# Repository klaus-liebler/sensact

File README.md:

# sensact
Smarthome system - hardware, firmware, visualization

## Architektur
* Verteiltes System. Modellbasierte Codeerzeugung.
* Grundlage ist `firmware/sensact_firmware/builder/Models/` (Phase `GenerateModelFiles`).
  Hier ein Projekt analog Beispielprojekt "Sattlerstrasse16" anlegen (s.
  `firmware/sensact_firmware/docs/build-process.md`).
* Kleinste Einheit ist eine "Application", die eine eindeutige ID besitzt. Beispiele für Applications sind "Taster", "Drehencoder", "Jalousie" oder "PWM-Licht"

## Hardware
1. SensactHS: Hutschienenmontage
1. SensactUP: Unterputzmontage

## Kommunikation zwischen den Knoten
Die Knoten sind über einen gemeinsamen CAN-Bus verbunden.

### Altes Nachrichtenformat ()
TBD

### Neues Nachrichtenformat

Es gibt vier Namespaces für Nachrichten "REQUEST" und "RESPONSE", "EVENT" und "ACKNOWLEDGE". Dies wird mit den beiden LSB des Versions-Namespace-Bytes erklärt (Somit bleiben 64 Versionierungsmöglichkeiten)
Alle vier Namespaces haben ihren eigenen counter. Dieser beginnt bei 0x0 mit der ersten versendeten Nachricht und läuft nach 255 (0xFF) wieder auf 0. Die Ready-Nachricht wird immer mit counter=0x0 übertragen. Sie darf verwendet werden, um die Kommunikations-Session abzubrechen und die counter neu zu starten. Die counter representieren gemeinsames Wissen von Master und Slave  
REQEST (0b00): Vom Master zum Slave.
RESPONSE (0b01): Antwort auf REQUEST
EVENT (0b10): Vom Slave zum Master
ACKNOWLEDGE (0b11): Antwort des Masters auf ein Event

REQUEST
0x00: "HEARTBEAT": Board gibt Heartbeat zurück
0x01: "IDENTIFY: 
0x02: "SEND_CAN":

RESPONSE
In der Response wird einfach die ID des Requests übernommen. Häufig wird dann ein REQUEST-spezifischer Fehlercode als uint32-t zurück geliefert. Eine 0x0 steht dann per Konvention für eine fehlerfreie Verarbeitung. Ggf. werden in Zukunft WELL_KNOWN_ERROR_CODES definiert.
0x01: UNEXPECTED_COUNTER
0x02: CRC_ERROR

Alle Responses, die nicht nur einen reinen Error-Code, sondern spezifischere Daten zurück liefern, werden im folgenden beschrieben  
0x01: "IDENTIFY": Board gibt Board-Typ u16. NodeID u16 und ID des Chips u96 (?) zurück.

EVENTS
00 "READY" Slave meldet sich nach dem Booten und gibt an, dass er jetzt für Befehle aller Art bereit steht. Beginn einer Session. Alle counter werden auf 0 gesetzt, außer der EVENT_COUNTER - der muss nun auf 1 stehen
02 "CAN_RECEIVED": Slave zeigt an, dass er eine CAN-Nachricht empfangen (besser: auf dem Bus mitgelesen) hat

ACKNOWLEDGES:
Der Slave kann bei ausbleibendem Acknowledge die Nachricht nochmals versenden

## WebUI

### Konzept

Auf einer Website sollen alle Apps einer Node mit commands versehen werden können
Jeder Host hat eine Bedienoberfläche
Problem: Wird die Bedienoberfläche zur Laufzeit von den Hosts und ihren Unterobjekten generiert (a) HTML oder b)JSON) oder kennt die WebUI bereits alle Objekte
Kennt die WebUI die Objekte auch semantisch oder kann Sie nur eine HTML-GUI aufbauen zur Erzeugung von CAN-Bus-Nachrichten 
Denkweise: Die WebUI kann CAN-Nachrichten erzeugen und so an die Node senden, wie sie auch über den CAN-Bus an der Node ankommen würden. Es muss ein JSON generiert werden, das zur Erzeugung einer HTML-UI verwendet werden kann, die dann eben genau diese Nachrichten sendet
Die WebUI kennt bereits alle Applications, die in der Node vorhanden sind. Dazu wird neben der C++-Instanzierung auch TypeScript-Code aufgebaut, der die entsprechenden Objekte aufbaut
Für Buttons und RotEnc gibt es die Möglichkeit, die Beträtigung zu simulieren. Dazu wird dann einfach jene Nachricht auf den MessageBus gelegt, die auch in Wirklichkeit vrsendet wird
An Aktoren können jene Commands versendet werden mitsamt notwendiger Parameter
Für die Erstellung eines Command

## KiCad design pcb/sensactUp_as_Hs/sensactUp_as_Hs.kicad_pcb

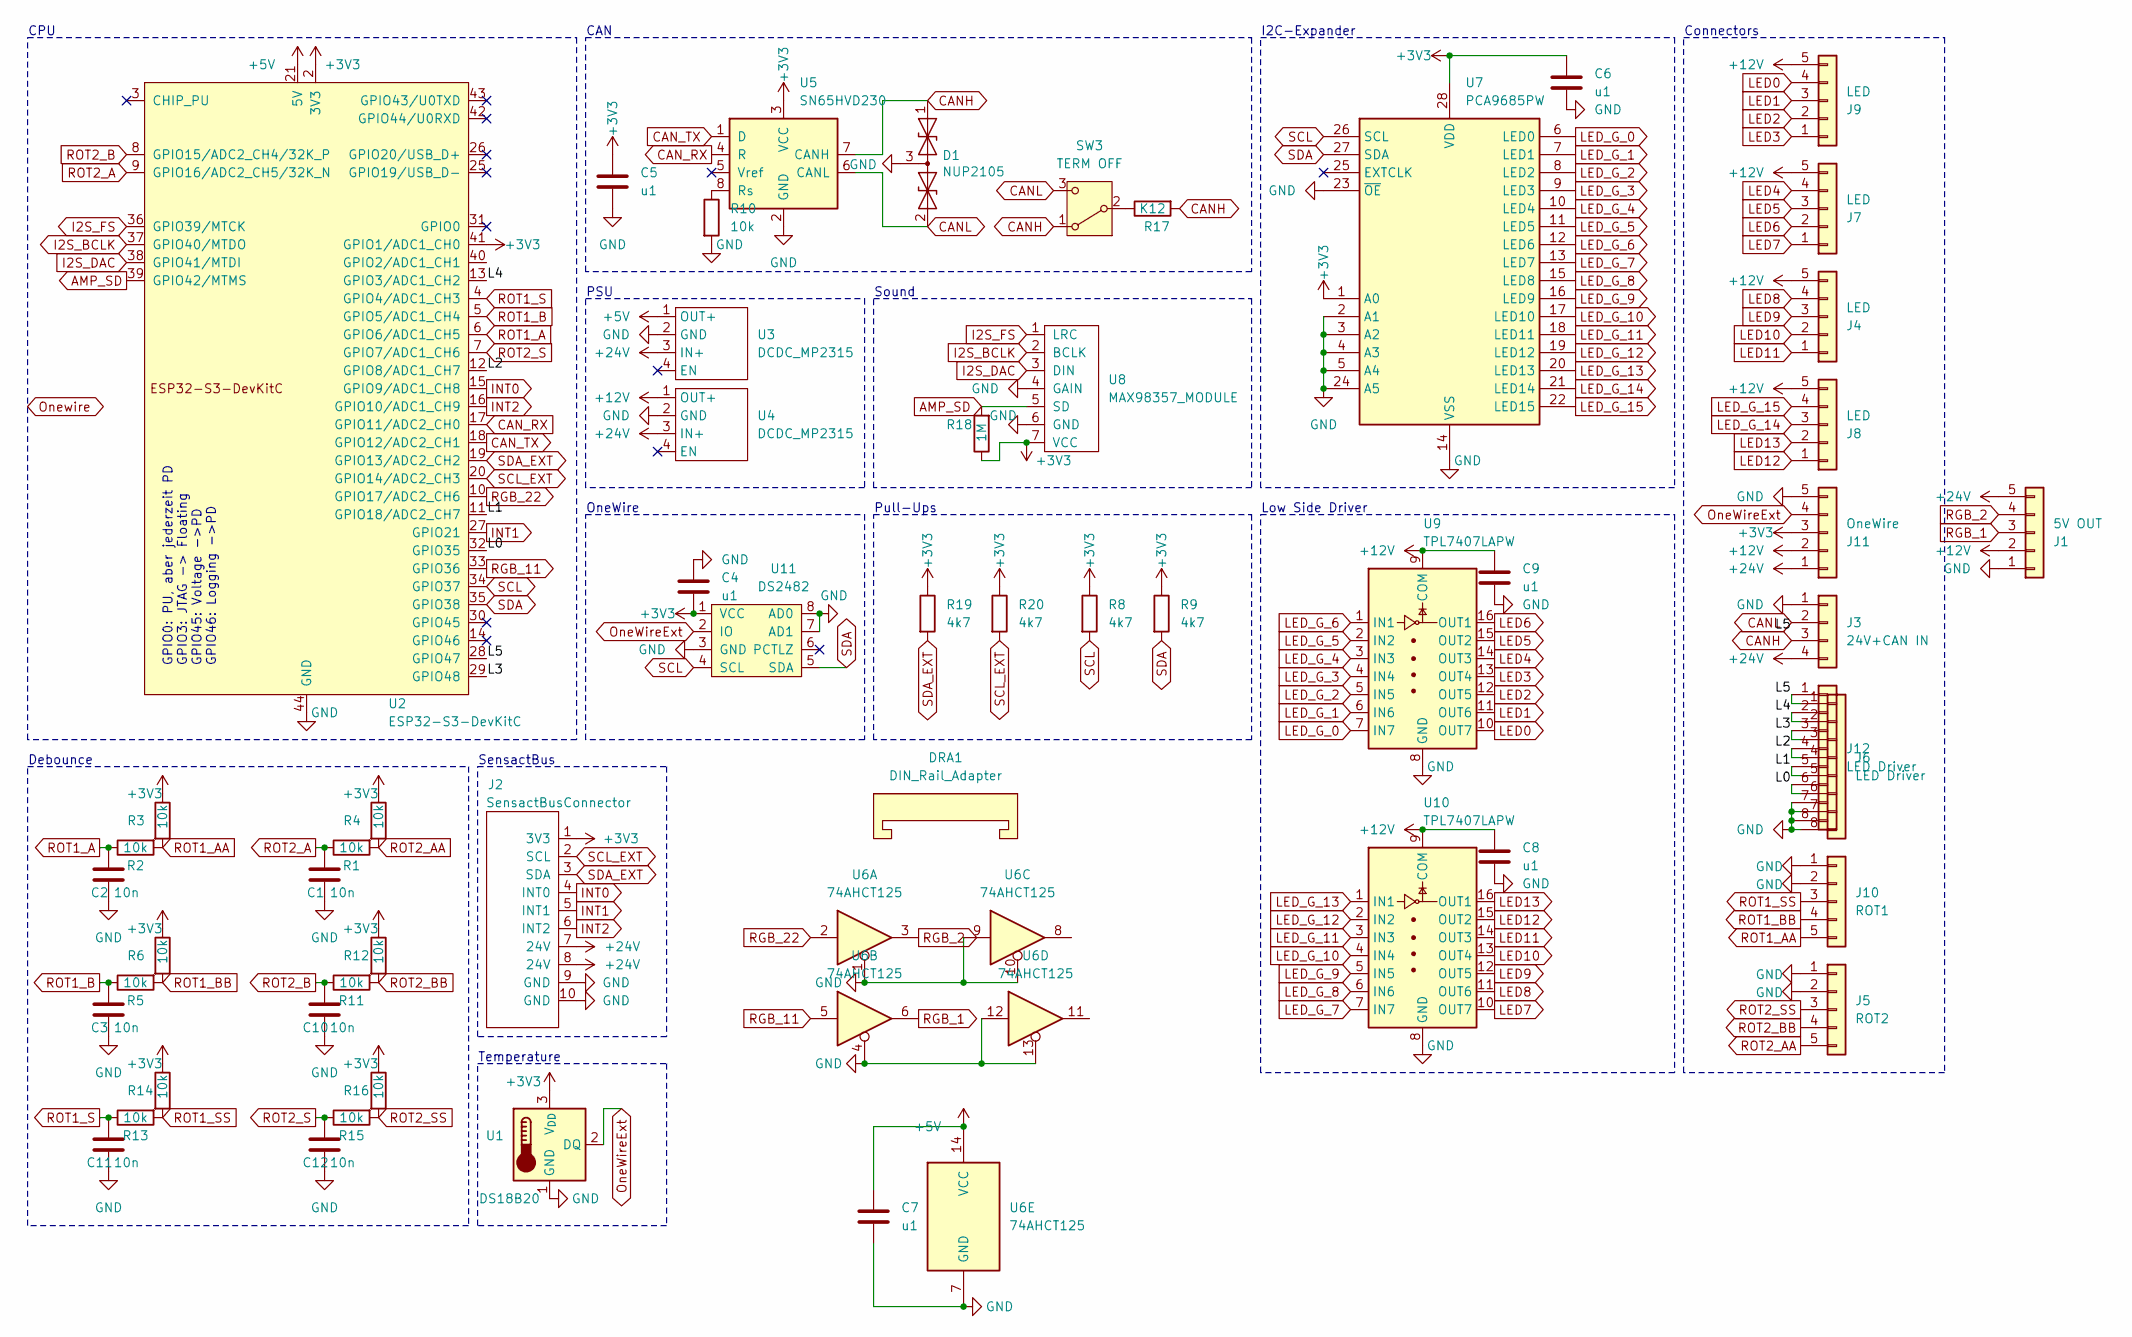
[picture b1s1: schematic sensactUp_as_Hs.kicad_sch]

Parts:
C1, C2, C3, C10, C11, C12: 10n; C_0805_2012Metric_Pad1.18x1.45mm_HandSolder
C4, C5, C6, C7, C8, C9: u1; C_0805_2012Metric_Pad1.18x1.45mm_HandSolder
D1: NUP2105; SOT-23_Handsoldering; MPN NUP2105L
DRA1: DIN_Rail_Adapter; Camdenboss CNMB-6
J1: 5V OUT; PhoenixContact_MCV_1,5_5-G-3.81_1x05_P3.81mm_Vertical_small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
J2: SensactBusConnector; IDC-Header_2x05_P2.54mm_Horizontal
J3: 24V+CAN IN; PhoenixContact_MCV_1,5_4-G-3.5_1x04_P3.50mm_Vertical_smalle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
J4, J7, J8, J9: LED; PhoenixContact_MCV_1,5_5-G-3.81_1x05_P3.81mm_Vertical_small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
J5: ROT2; PhoenixContact_MCV_1,5_5-G-3.81_1x05_P3.81mm_Vertical_small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
J6: LED Driver; PhoenixContact_MC_0,5_8-G-2.5_1x08_P2.50mm_Horizontal
J10: ROT1; PhoenixContact_MCV_1,5_5-G-3.81_1x05_P3.81mm_Vertical_small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
J11: OneWire; PhoenixContact_MCV_1,5_5-G-3.81_1x05_P3.81mm_Vertical_small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
J12: LED Driver; PinHeader_1x08_P2.54mm_Vertical
R1, R2, R3, R4, R5, R6, R10, R11, R12, R13, R14, R15, R16: 10k; R_0805_2012Metric_Pad1.20x1.40mm_HandSolder
R8, R9, R19, R20: 4k7; R_0805_2012Metric_Pad1.20x1.40mm_HandSolder
R17: K12; R_1206_3216Metric_Pad1.30x1.75mm_HandSolder; MPN 1206W4F1200T5E
R18: 1M; R_0805_2012Metric_Pad1.20x1.40mm_HandSolder
SW3: TERM OFF; Switch_SS12D00
U1: DS18B20; TO-92L_HandSolder
U2: ESP32-S3-DevKitC; ESP32-S3 chinese dev board
U3, U4: DCDC_MP2315; DCDC_MP2315_horizontal
U5: SN65HVD230; SOIC-8_3.9x4.9mm_P1.27mm
U6: 74AHCT125; SOIC-14_3.9x8.7mm_P1.27mm_handsolder
U7: PCA9685PW; TSSOP-28_4.4x9.7mm_Pitch0.65mm_handsolder
U8: MAX98357_MODULE; PinHeader_1x07_P2.54mm_Vertical
U9, U10: TPL7407LAPW; TSSOP-16_4.4x5mm_P0.65mm
U11: DS2482; SOIC-8_3.9x4.9mm_P1.27mm_handsolder

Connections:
+3V3: C4.1, C5.1, C6.1, J2.1 (3V3), J11.3, R3.1, R4.1, R6.1, R8.1, R9.1, R12.1, R14.1, R16.1, R18.1, R19.1, R20.1, U1.3 (V_{DD}), U2.1 (3V3), U2.2 (3V3), U2.41 (GPIO1/ADC1_CH0), U5.3 (VCC), U7.1 (A0), U7.28 (VDD), U8.7 (VCC), U11.1 (VCC)
+5V: C7.2, U2.21 (5V), U3.1 (OUT+), U6.14 (VCC)
+12V: C8.1, C9.1, J1.2, J4.5, J7.5, J8.5, J9.5, J11.2, U4.1 (OUT+), U9.9 (COM), U10.9 (COM)
+24V: J1.5, J2.7 (24V), J2.8 (24V), J3.4, J11.1, U3.3 (IN+), U4.3 (IN+)
/L0: J6.6, J12.6, U2.32 (GPIO35)
/L1: J6.5, J12.5, U2.11 (GPIO18/ADC2_CH7)
/L2: J6.4, J12.4, U2.12 (GPIO8/ADC1_CH7)
/L3: J6.3, J12.3, U2.29 (GPIO48)
/L4: J6.2, J12.2, U2.13 (GPIO3/ADC1_CH2)
/L5: J6.1, J12.1, U2.28 (GPIO47)
AMP_SD: R18.2, U2.39 (GPIO42/MTMS), U8.5 (SD)
CANH: D1.1 (A1), J3.3, R17.2, SW3.1 (A), U5.7 (CANH)
CANL: D1.2 (A2), J3.2, SW3.3 (C), U5.6 (CANL)
CAN_RX: U2.17 (GPIO11/ADC2_CH0), U5.4 (R)
CAN_TX: U2.18 (GPIO12/ADC2_CH1), U5.1 (D)
GND: C1.1, C2.1, C3.1, C4.2, C5.2, C6.2, C7.1, C8.2, C9.2, C10.1, C11.1, C12.1, D1.3 (common), J1.1, J2.9 (GND), J2.10 (GND), J3.1, J5.1, J5.2, J6.7, J6.8, J10.1, J10.2, J11.5, J12.7, J12.8, R10.2, U1.1 (GND), U2.22 (GND), U2.23 (GND), U2.24 (GND), U2.44 (GND), U3.2 (GND), U4.2 (GND), U5.2 (GND), U6.1, U6.4, U6.7 (GND), U6.9, U6.10, U6.12, U6.13, U7.2 (A1), U7.3 (A2), U7.4 (A3), U7.5 (A4), U7.14 (VSS), U7.23 (~OE), U7.24 (A5), U8.4 (GAIN), U8.6 (GND), U9.8 (GND), U10.8 (GND), U11.3 (GND), U11.7 (AD1), U11.8 (AD0)
I2S_BCLK: U2.37 (GPIO40/MTDO), U8.2 (BCLK)
I2S_DAC: U2.38 (GPIO41/MTDI), U8.3 (DIN)
I2S_FS: U2.36 (GPIO39/MTCK), U8.1 (LRC)
INT0: J2.4 (INT0), U2.15 (GPIO9/ADC1_CH8)
INT1: J2.5 (INT1), U2.27 (GPIO21)
INT2: J2.6 (INT2), U2.16 (GPIO10/ADC1_CH9)
LED0: J9.4, U9.10 (OUT7)
LED1: J9.3, U9.11 (OUT6)
LED2: J9.2, U9.12 (OUT5)
LED3: J9.1, U9.13 (OUT4)
LED4: J7.4, U9.14 (OUT3)
LED5: J7.3, U9.15 (OUT2)
LED6: J7.2, U9.16 (OUT1)
LED7: J7.1, U10.10 (OUT7)
LED8: J4.4, U10.11 (OUT6)
LED9: J4.3, U10.12 (OUT5)
LED10: J4.2, U10.13 (OUT4)
LED11: J4.1, U10.14 (OUT3)
LED12: J8.1, U10.15 (OUT2)
LED13: J8.2, U10.16 (OUT1)
LED_G_0: U7.6 (LED0), U9.7 (IN7)
LED_G_1: U7.7 (LED1), U9.6 (IN6)
LED_G_2: U7.8 (LED2), U9.5 (IN5)
LED_G_3: U7.9 (LED3), U9.4 (IN4)
LED_G_4: U7.10 (LED4), U9.3 (IN3)
LED_G_5: U7.11 (LED5), U9.2 (IN2)
LED_G_6: U7.12 (LED6), U9.1 (IN1)
LED_G_7: U7.13 (LED7), U10.7 (IN7)
LED_G_8: U7.15 (LED8), U10.6 (IN6)
LED_G_9: U7.16 (LED9), U10.5 (IN5)
LED_G_10: U7.17 (LED10), U10.4 (IN4)
LED_G_11: U7.18 (LED11), U10.3 (IN3)
LED_G_12: U7.19 (LED12), U10.2 (IN2)
LED_G_13: U7.20 (LED13), U10.1 (IN1)
LED_G_14: J8.3, U7.21 (LED14)
LED_G_15: J8.4, U7.22 (LED15)
unnamed: R17.1, SW3.2 (B)
unnamed: R10.1, U5.8 (Rs)
OneWireExt: J11.4, U1.2 (DQ), U11.2 (IO)
RGB_1: J1.3, U6.6
RGB_2: J1.4, U6.3
RGB_11: U2.33 (GPIO36), U6.5
RGB_22: U2.10 (GPIO17/ADC2_CH6), U6.2
ROT1_A: C2.2, R2.1, U2.6 (GPIO6/ADC1_CH5)
ROT1_AA: J10.5, R2.2, R3.2
ROT1_B: C3.2, R5.1, U2.5 (GPIO5/ADC1_CH4)
ROT1_BB: J10.4, R5.2, R6.2
ROT1_S: C11.2, R13.1, U2.4 (GPIO4/ADC1_CH3)
ROT1_SS: J10.3, R13.2, R14.2
ROT2_A: C1.2, R1.1, U2.9 (GPIO16/ADC2_CH5/32K_N)
ROT2_AA: J5.5, R1.2, R4.2
ROT2_B: C10.2, R11.1, U2.8 (GPIO15/ADC2_CH4/32K_P)
ROT2_BB: J5.4, R11.2, R12.2
ROT2_S: C12.2, R15.1, U2.7 (GPIO7/ADC1_CH6)
ROT2_SS: J5.3, R15.2, R16.2
SCL: R8.2, U2.34 (GPIO37), U7.26 (SCL), U11.4 (SCL)
SCL_EXT: J2.2 (SCL), R20.2, U2.20 (GPIO14/ADC2_CH3)
SDA: R9.2, U2.35 (GPIO38), U7.27 (SDA), U11.5 (SDA)
SDA_EXT: J2.3 (SDA), R19.2, U2.19 (GPIO13/ADC2_CH2)

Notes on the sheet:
GPIO0: PU, aber jederzeit PD GPIO3: JTAG -> Floating GPIO45: Voltage ->PD GPIO46: Logging ->PD
Low Side Driver
OneWire
Sound
CAN
Pull-Ups
I2C-Expander
Debounce
SensactBus
CPU
PSU
Connectors
Temperature

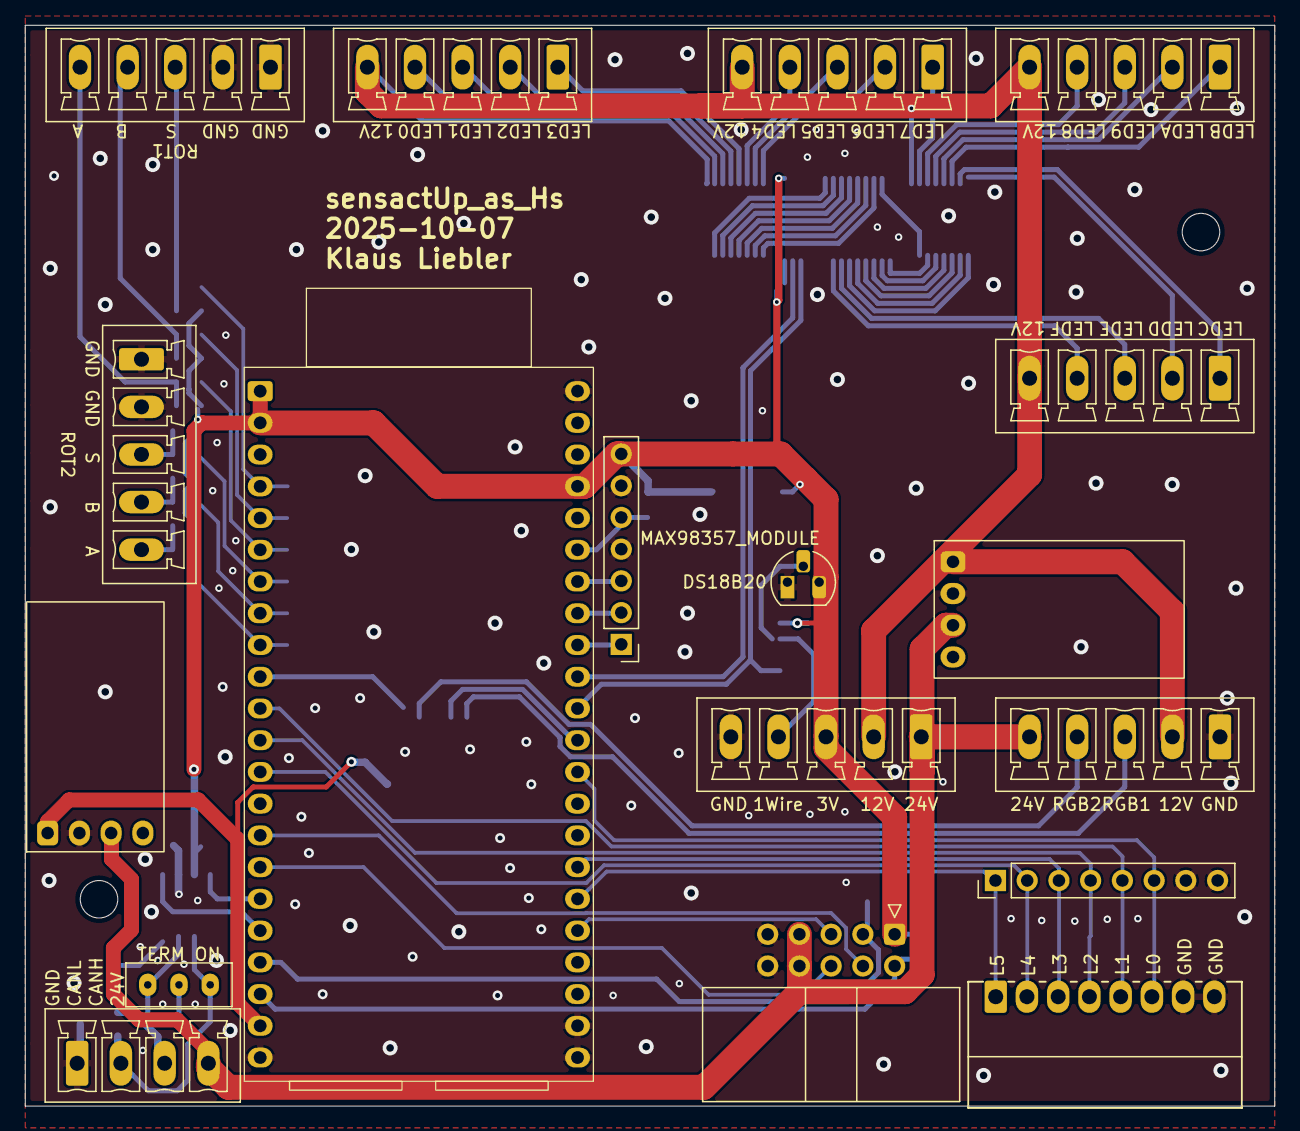
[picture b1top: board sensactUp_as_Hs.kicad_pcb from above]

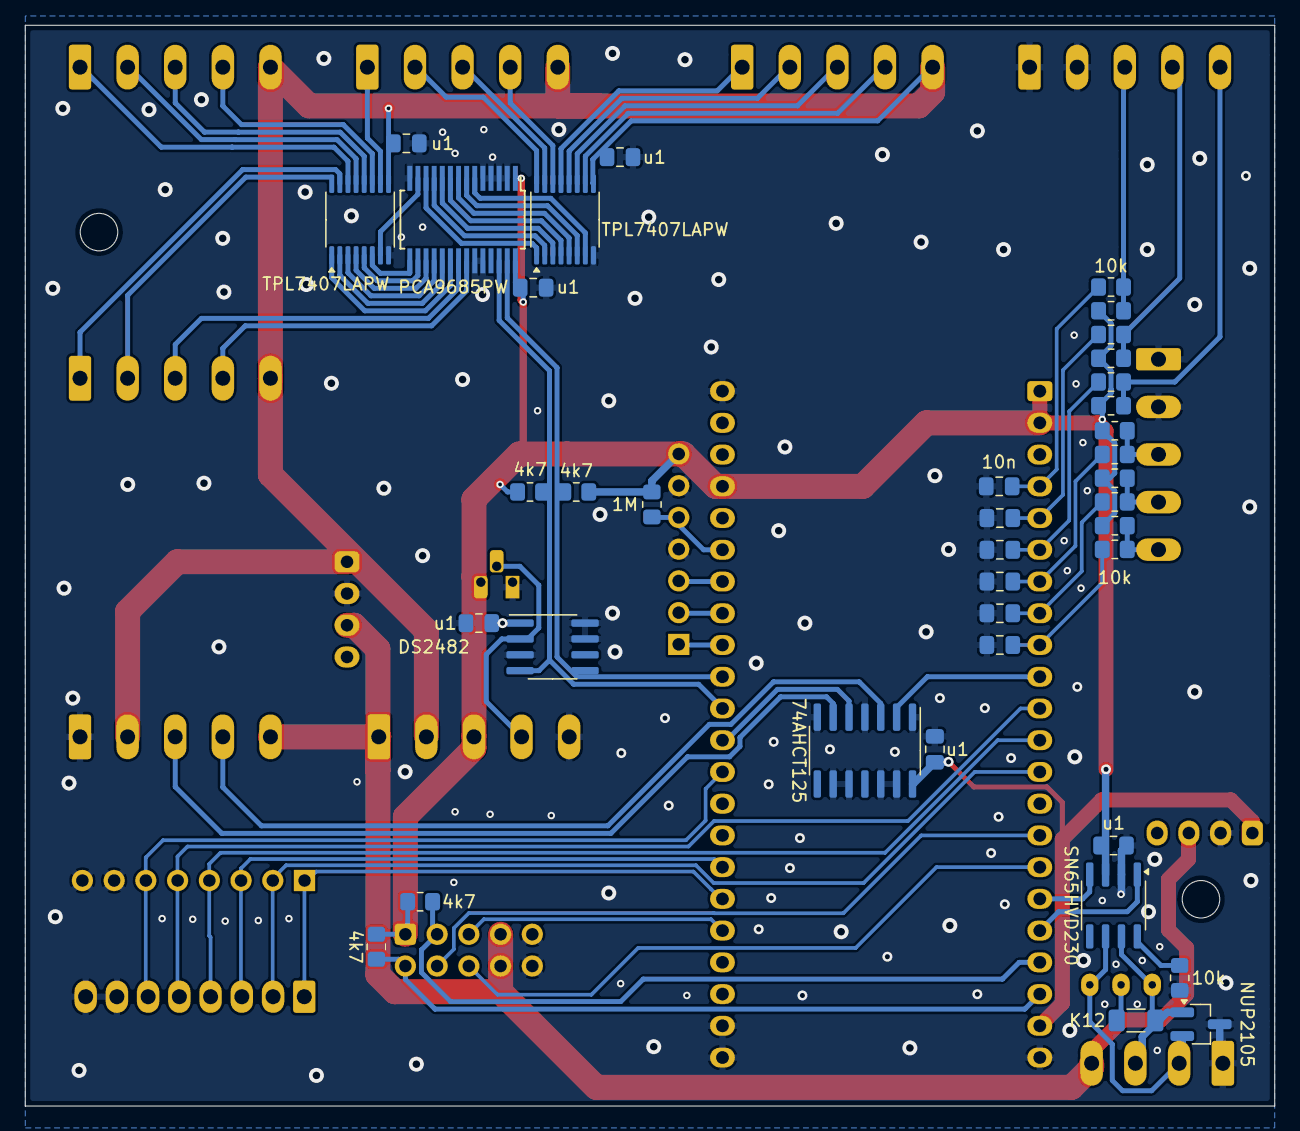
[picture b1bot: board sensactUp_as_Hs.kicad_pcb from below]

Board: 2 copper layers, 100.0 x 86.5 mm, 57 parts (38 on the bottom side), 75 nets.

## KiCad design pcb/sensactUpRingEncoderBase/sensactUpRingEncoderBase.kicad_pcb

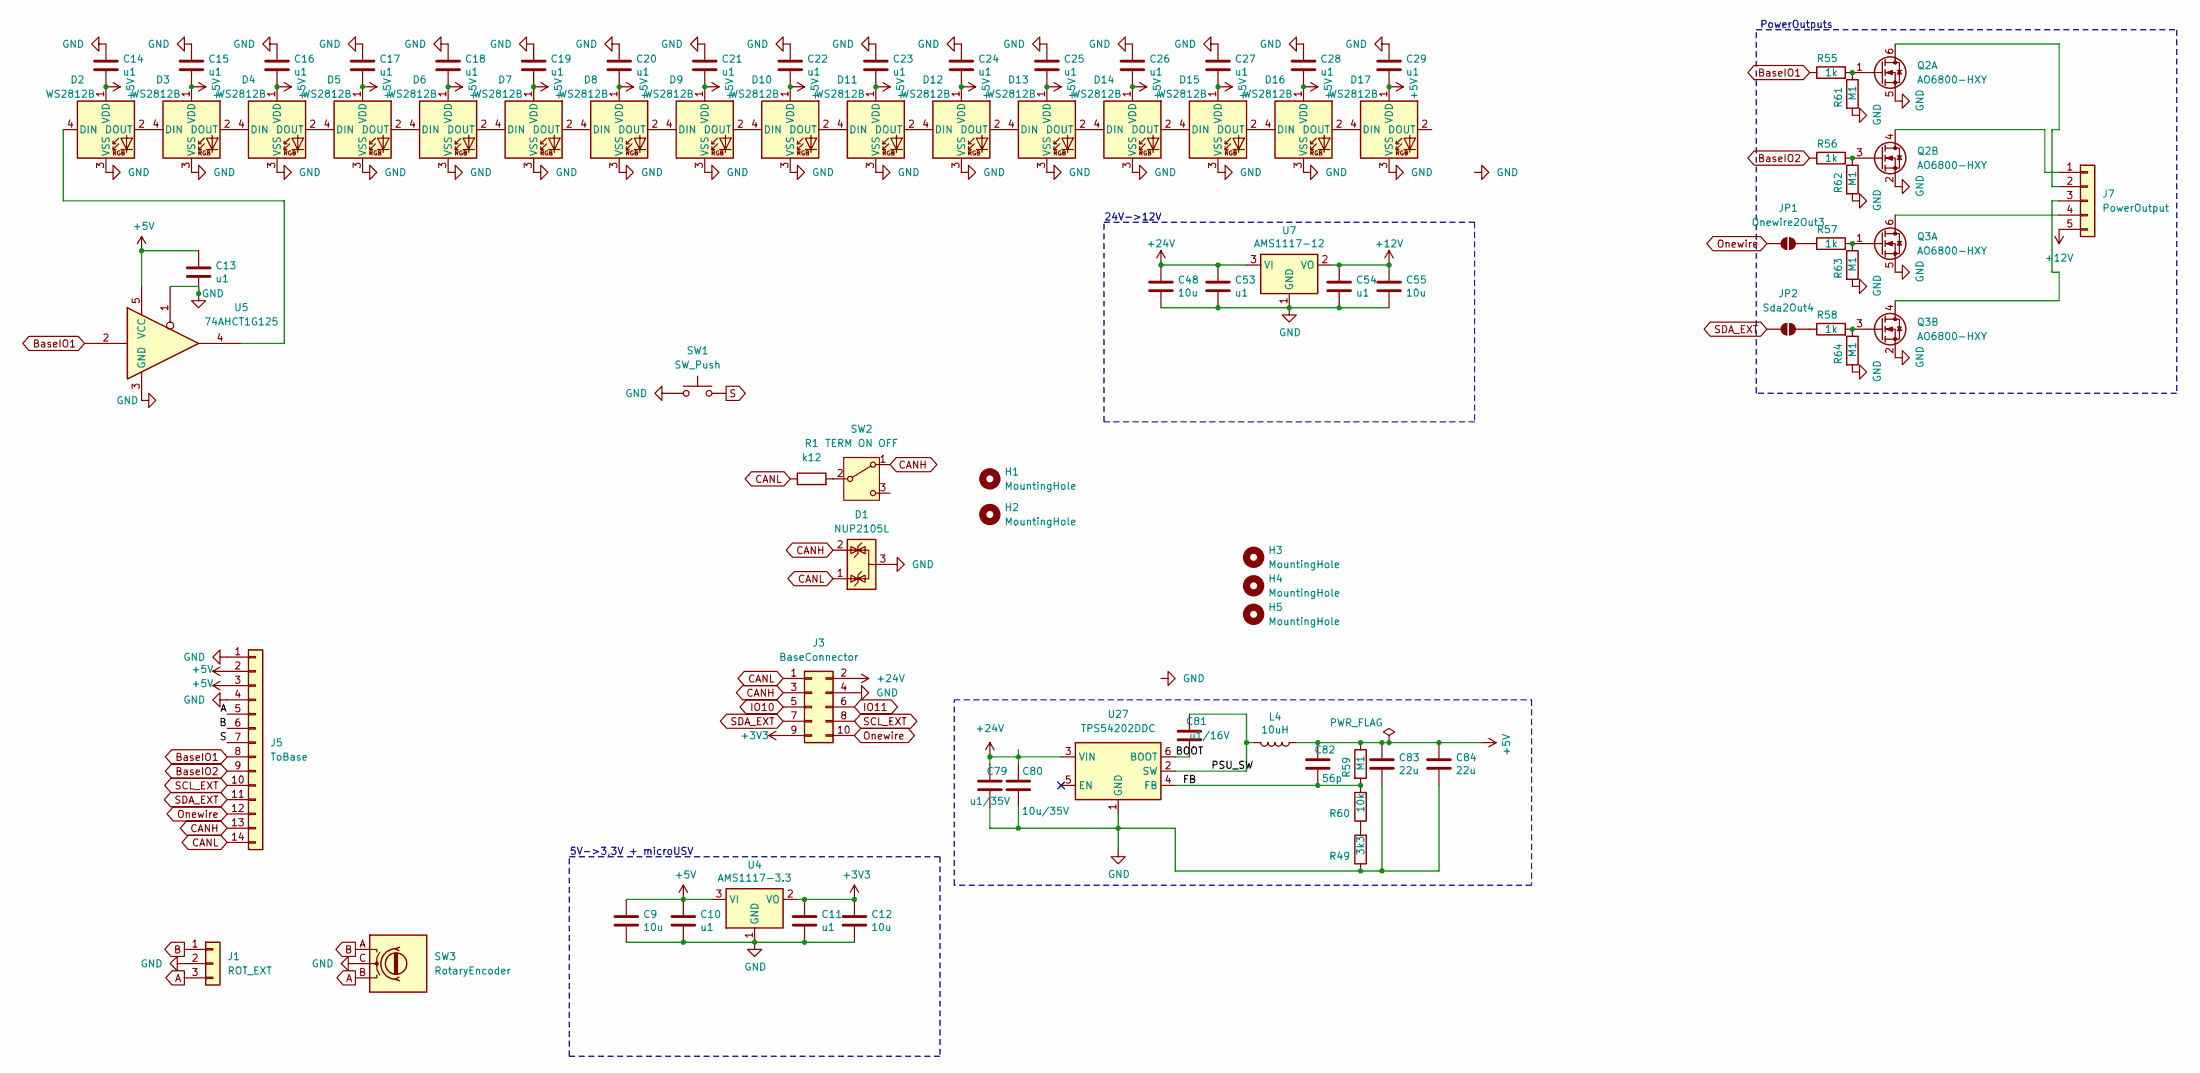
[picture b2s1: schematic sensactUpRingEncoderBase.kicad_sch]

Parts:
C9, C12, C48, C55: 10u; C_0805_2012Metric_Pad1.18x1.45mm_HandSolder
C10, C11, C13, C14, C15, C16, C17, C18, C19, C20, C21, C22, C23, C24, C25, C26, C27, C28, C29, C53, C54: u1; C_0805_2012Metric_Pad1.18x1.45mm_HandSolder
C79: u1/35V; R_0805_2012Metric_Pad1.20x1.40mm_HandSolder; MPN CC0603KRX7R9BB104
C80: 10u/35V; C_1206_3216Metric_Pad1.33x1.80mm_HandSolder; MPN CGA0805X5R106K350MT
C81: u1/16V; R_0805_2012Metric_Pad1.20x1.40mm_HandSolder; MPN CC0603KRX7R9BB104
C82: 56p; R_0805_2012Metric_Pad1.20x1.40mm_HandSolder; MPN CC0402JRNPO9BN560
C83, C84: 22u; R_0805_2012Metric_Pad1.20x1.40mm_HandSolder; MPN CL10A226MP8NUNE
D1: NUP2105L; SOT-23_Handsoldering
D2, D3, D4, D5, D6, D7, D8, D9, D10, D11, D12, D13, D14, D15, D16, D17: WS2812B; LED_WS2812B-Mini_PLCC4_3.5x3.5mm
H1, H2: MountingHole; MountingHole_5mm
H3, H4, H5: MountingHole; MountingHole_2.2mm_M2
J1: ROT_EXT; PhoenixContact_MCV_1,5_3-G-3.5_1x03_P3.50mm_Vertical_smalle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
J3: BaseConnector; IDC-Header_2x05_P2.54mm_Vertical
J5: ToBase; Hirose_FH12-14S-0.5SH_1x14-1MP_P0.50mm_Horizontal_handsolder
J7: PowerOutput; PinHeader_1x05_P2.54mm_Vertical
JP1: Onewire2Out3; SolderJumper-2_P1.3mm_Open_RoundedPad1.0x1.5mm
JP2: Sda2Out4; SolderJumper-2_P1.3mm_Open_RoundedPad1.0x1.5mm
L4: 10uH; L_0630; MPN FXL0630-100-M
Q2, Q3: AO6800-HXY; SOT-23-6_Handsoldering
R1: k12; R_0805_2012Metric_Pad1.20x1.40mm_HandSolder
R49: 3k3; R_0805_2012Metric_Pad1.20x1.40mm_HandSolder; MPN 0402WGF3301TCE
R55, R56, R57, R58: 1k; R_0805_2012Metric_Pad1.20x1.40mm_HandSolder
R59, R61, R62, R63, R64: M1; R_0805_2012Metric_Pad1.20x1.40mm_HandSolder; MPN 0201WMF1003TEE
R60: 10k; R_0805_2012Metric_Pad1.20x1.40mm_HandSolder; MPN 0201WMF1002TEE
SW1: SW_Push; Button_12mm_ANCHOR_CENTER
SW2: TERM ON OFF; SW_SPDT_PCM12_handsolder
SW3: RotaryEncoder; Encoder Alps-Alpine EC35
U4: AMS1117-3.3; SOT-223-3_TabPin2_HANDSOLDER
U5: 74AHCT1G125; SOT-353_SC-70-5_Handsoldering
U7: AMS1117-12; SOT-223-3_TabPin2_HANDSOLDER
U27: TPS54202DDC; SOT-23-6_Handsoldering; MPN TPS54202DDCR

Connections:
+3V3: C11.1, C12.1, J3.9, U4.2 (VO)
+5V: C9.1, C10.1, C13.1, C14.2, C15.2, C16.2, C17.2, C18.2, C19.2, C20.2, C21.2, C22.2, C23.2, C24.2, C25.2, C26.2, C27.2, C28.2, C29.2, C82.2, C83.1, C84.1, D2.1 (VDD), D3.1 (VDD), D4.1 (VDD), D5.1 (VDD), D6.1 (VDD), D7.1 (VDD), D8.1 (VDD), D9.1 (VDD), D10.1 (VDD), D11.1 (VDD), D12.1 (VDD), D13.1 (VDD), D14.1 (VDD), D15.1 (VDD), D16.1 (VDD), D17.1 (VDD), J5.2, J5.3, L4.1, R59.1, U4.3 (VI), U5.5 (VCC)
+12V: C54.1, C55.1, J7.5, U7.2 (VO)
+24V: C48.1, C53.1, C79.2, C80.2, J3.2, U7.3 (VI), U27.3 (VIN)
/BOOT: C81.1, U27.6 (BOOT)
/FB: C82.1, R59.2, R60.2, U27.4 (FB)
/PSU_SW: C81.2, L4.2, U27.2 (SW)
A: J1.3, J5.5, SW3.B
B: J1.1, J5.6, SW3.A
BaseIO1: J5.8, R55.1, U5.2
BaseIO2: J5.9, R56.1
CANH: D1.2 (K), J3.3, J5.13, SW2.1 (A)
CANL: D1.1 (K), J3.1, J5.14, R1.1
GND: C9.2, C10.2, C11.2, C12.2, C13.2, C14.1, C15.1, C16.1, C17.1, C18.1, C19.1, C20.1, C21.1, C22.1, C23.1, C24.1, C25.1, C26.1, C27.1, C28.1, C29.1, C48.2, C53.2, C54.2, C55.2, C79.1, C80.1, C83.2, C84.2, D1.3 (A), D2.3 (VSS), D3.3 (VSS), D4.3 (VSS), D5.3 (VSS), D6.3 (VSS), D7.3 (VSS), D8.3 (VSS), D9.3 (VSS), D10.3 (VSS), D11.3 (VSS), D12.3 (VSS), D13.3 (VSS), D14.3 (VSS), D15.3 (VSS), D16.3 (VSS), D17.3 (VSS), J1.2, J3.4, J5.1, J5.4, Q2.2 (S), Q2.5 (S), Q3.2 (S), Q3.5 (S), R49.1, R61.2, R62.2, R63.2, R64.2, SW1.1, SW3.C, U4.1 (GND), U5.1, U5.3 (GND), U7.1 (GND), U27.1 (GND)
IO10: J3.5
IO11: J3.6
unnamed: D2.4 (DIN), U5.4
unnamed: D2.2 (DOUT), D3.4 (DIN)
unnamed: D3.2 (DOUT), D4.4 (DIN)
unnamed: D4.2 (DOUT), D5.4 (DIN)
unnamed: D5.2 (DOUT), D6.4 (DIN)
unnamed: D6.2 (DOUT), D7.4 (DIN)
unnamed: D7.2 (DOUT), D8.4 (DIN)
unnamed: D8.2 (DOUT), D9.4 (DIN)
unnamed: D9.2 (DOUT), D10.4 (DIN)
unnamed: D10.2 (DOUT), D11.4 (DIN)
unnamed: D11.2 (DOUT), D12.4 (DIN)
unnamed: D12.2 (DOUT), D13.4 (DIN)
unnamed: D13.2 (DOUT), D14.4 (DIN)
unnamed: D14.2 (DOUT), D15.4 (DIN)
unnamed: D15.2 (DOUT), D16.4 (DIN)
unnamed: D16.2 (DOUT), D17.4 (DIN)
unnamed: J7.1, Q2.4 (D)
unnamed: J7.2, Q2.6 (D)
unnamed: J7.3, Q3.4 (D)
unnamed: J7.4, Q3.6 (D)
unnamed: JP1.2 (B), R57.1
unnamed: JP2.2 (B), R58.1
unnamed: Q2.1 (G), R55.2, R61.1
unnamed: Q2.3 (G), R56.2, R62.1
unnamed: Q3.1 (G), R57.2, R63.1
unnamed: Q3.3 (G), R58.2, R64.1
unnamed: R49.2, R60.1
unnamed: R1.2, SW2.2 (B)
Onewire: J3.10, J5.12, JP1.1 (A)
S: J5.7, SW1.2
SCL_EXT: J3.8, J5.10
SDA_EXT: J3.7, J5.11, JP2.1 (A)

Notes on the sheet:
PowerOutputs
5V->3,3V + microUSV
24V->12V

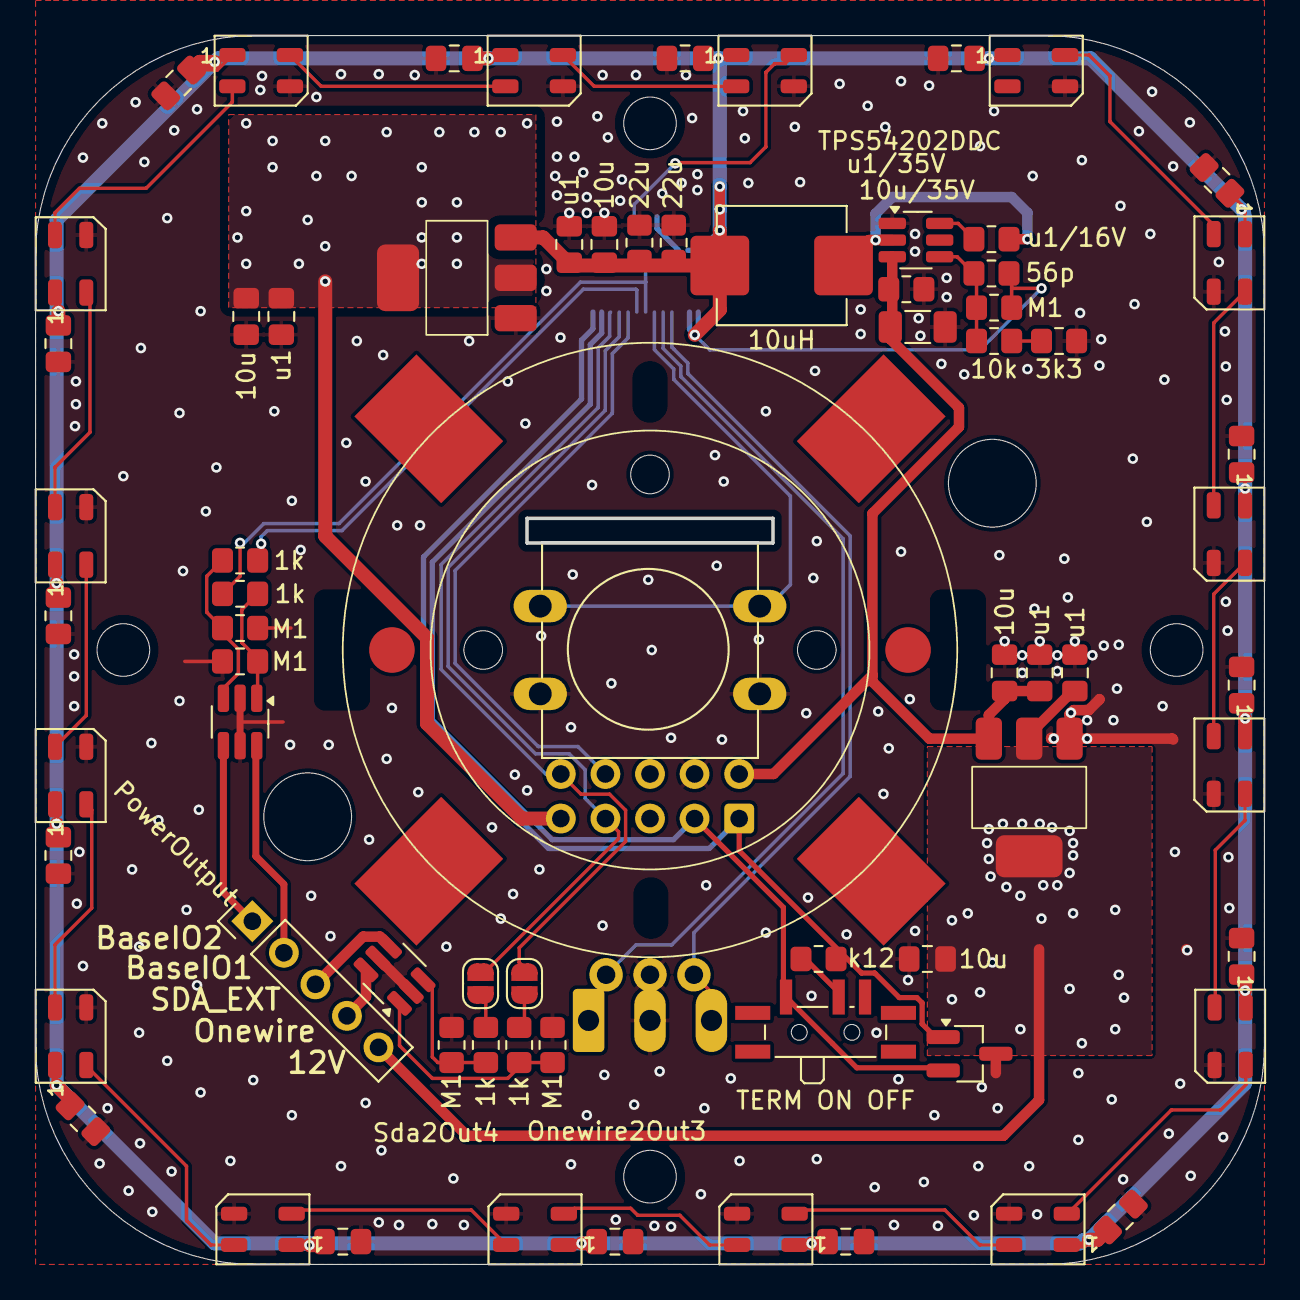
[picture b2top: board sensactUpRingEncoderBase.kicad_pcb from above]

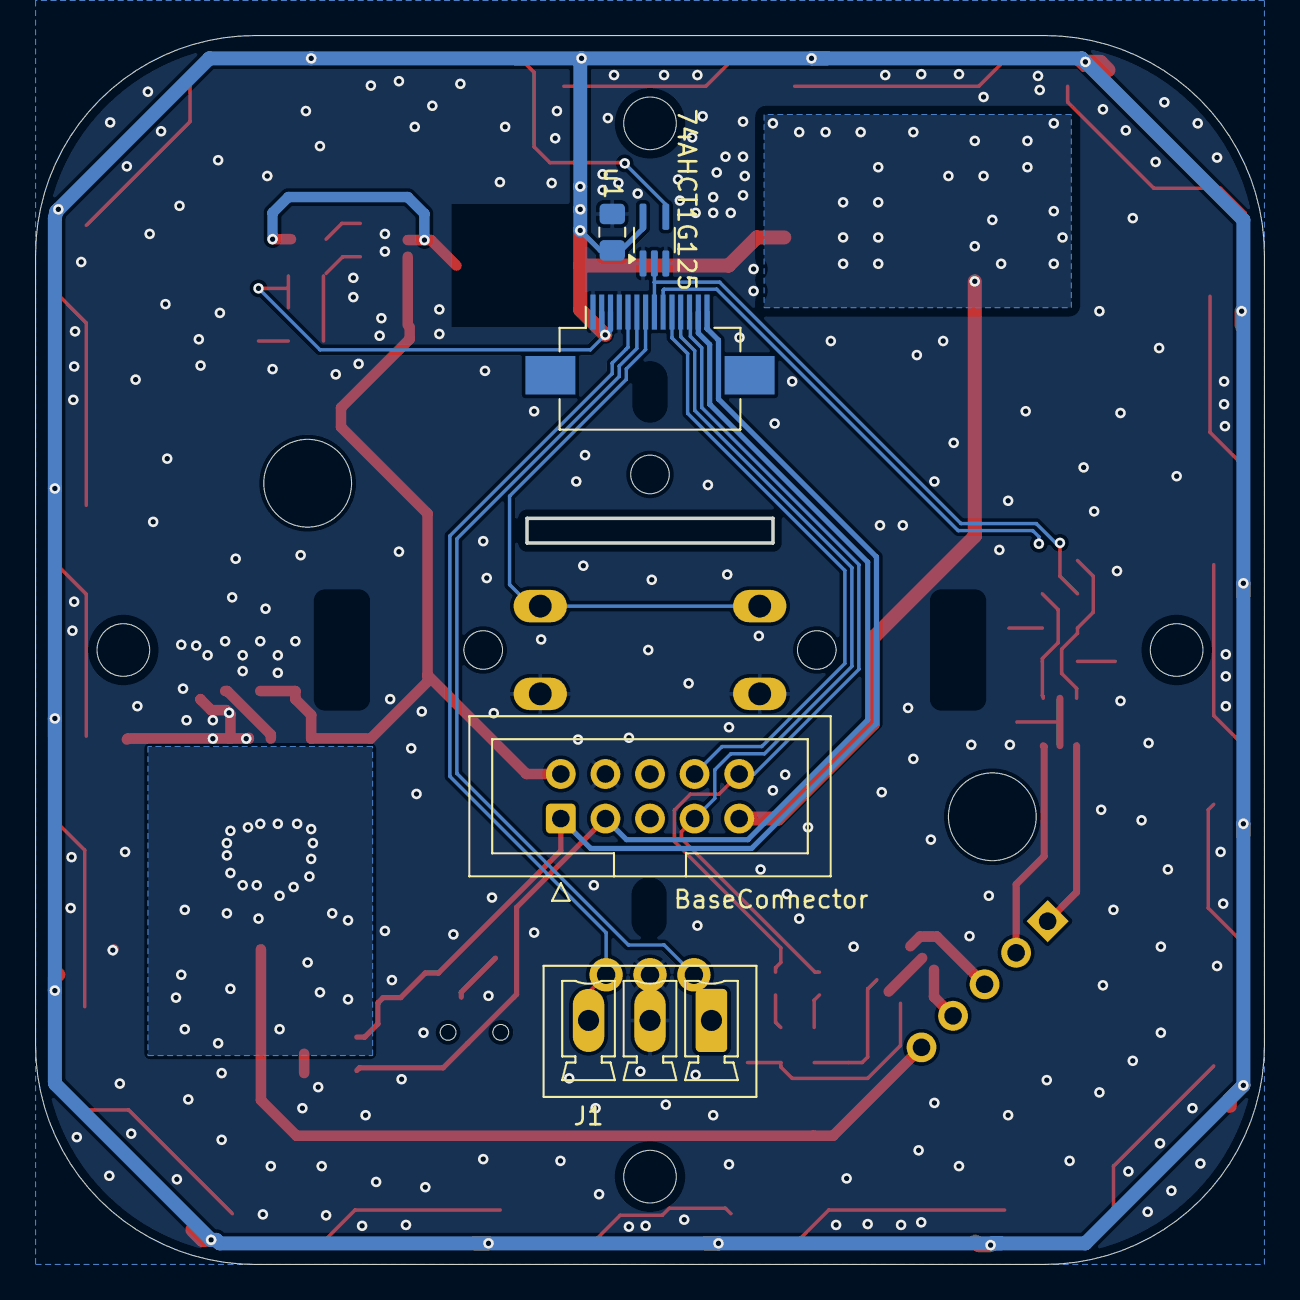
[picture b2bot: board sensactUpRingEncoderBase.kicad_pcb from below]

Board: 2 copper layers, 70.0 x 70.0 mm, 81 parts (5 on the bottom side), 46 nets.

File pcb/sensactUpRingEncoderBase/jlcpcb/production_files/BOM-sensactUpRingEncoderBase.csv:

Comment,Designator,Footprint,LCSC,Quantity
AMS1117-12,U7,SOT-223-3_TabPin2_HANDSOLDER,,1
ROT_EXT,J1,"PhoenixContact_MCV_1,5_3-G-3.5_1x03_P3.50mm_Vertical_smallerCourtyard",,1
10u,C55,C_0805_2012Metric_Pad1.18x1.45mm_HandSolder,,1
u1,C54,C_0805_2012Metric_Pad1.18x1.45mm_HandSolder,,1
u1,C53,C_0805_2012Metric_Pad1.18x1.45mm_HandSolder,,1
10u,C48,C_0805_2012Metric_Pad1.18x1.45mm_HandSolder,,1
BaseConnector,J3,IDC-Header_2x05_P2.54mm_Vertical,,1
AMS1117-3.3,U4,SOT-223-3_TabPin2_HANDSOLDER,,1
M1,R61,R_0805_2012Metric_Pad1.20x1.40mm_HandSolder,,1
M1,R62,R_0805_2012Metric_Pad1.20x1.40mm_HandSolder,,1
MountingHole,H5,MountingHole_2.2mm_M2,,1
SW_Push,SW1,Button_12mm_ANCHOR_CENTER,,1
u1,C15,C_0805_2012Metric_Pad1.18x1.45mm_HandSolder,,1
M1,R64,R_0805_2012Metric_Pad1.20x1.40mm_HandSolder,,1
u1,C20,C_0805_2012Metric_Pad1.18x1.45mm_HandSolder,,1
TERM ON OFF,SW2,SW_SPDT_PCM12_handsolder,,1
NUP2105L,D1,SOT-23_Handsoldering,,1
WS2812B,D6,LED_WS2812B-Mini_PLCC4_3.5x3.5mm,,1
MountingHole,H4,MountingHole_2.2mm_M2,,1
WS2812B,D12,LED_WS2812B-Mini_PLCC4_3.5x3.5mm,,1
MountingHole,H1,MountingHole_5mm,,1
WS2812B,D7,LED_WS2812B-Mini_PLCC4_3.5x3.5mm,,1
u1,C22,C_0805_2012Metric_Pad1.18x1.45mm_HandSolder,,1
WS2812B,D13,LED_WS2812B-Mini_PLCC4_3.5x3.5mm,,1
u1,C17,C_0805_2012Metric_Pad1.18x1.45mm_HandSolder,,1
u1/16V,C81,R_0805_2012Metric_Pad1.20x1.40mm_HandSolder,,1
u1/35V,C79,R_0805_2012Metric_Pad1.20x1.40mm_HandSolder,,1
k12,R1,R_0805_2012Metric_Pad1.20x1.40mm_HandSolder,,1
M1,R63,R_0805_2012Metric_Pad1.20x1.40mm_HandSolder,,1
3k3,R49,R_0805_2012Metric_Pad1.20x1.40mm_HandSolder,,1
WS2812B,D15,LED_WS2812B-Mini_PLCC4_3.5x3.5mm,,1
WS2812B,D4,LED_WS2812B-Mini_PLCC4_3.5x3.5mm,,1
u1,C23,C_0805_2012Metric_Pad1.18x1.45mm_HandSolder,,1
u1,C24,C_0805_2012Metric_Pad1.18x1.45mm_HandSolder,,1
WS2812B,D14,LED_WS2812B-Mini_PLCC4_3.5x3.5mm,,1
u1,C16,C_0805_2012Metric_Pad1.18x1.45mm_HandSolder,,1
1k,R57,R_0805_2012Metric_Pad1.20x1.40mm_HandSolder,,1
u1,C28,C_0805_2012Metric_Pad1.18x1.45mm_HandSolder,,1
22u,C84,R_0805_2012Metric_Pad1.20x1.40mm_HandSolder,,1
AO6800-HXY,Q3,SOT-23-6_Handsoldering,,1
WS2812B,D10,LED_WS2812B-Mini_PLCC4_3.5x3.5mm,,1
u1,C26,C_0805_2012Metric_Pad1.18x1.45mm_HandSolder,,1
PowerOutput,J7,PinHeader_1x05_P2.54mm_Vertical,,1
u1,C27,C_0805_2012Metric_Pad1.18x1.45mm_HandSolder,,1
WS2812B,D5,LED_WS2812B-Mini_PLCC4_3.5x3.5mm,,1
10u,C12,C_0805_2012Metric_Pad1.18x1.45mm_HandSolder,,1
u1,C29,C_0805_2012Metric_Pad1.18x1.45mm_HandSolder,,1
WS2812B,D16,LED_WS2812B-Mini_PLCC4_3.5x3.5mm,,1
MountingHole,H2,MountingHole_5mm,,1
WS2812B,D17,LED_WS2812B-Mini_PLCC4_3.5x3.5mm,,1
10uH,L4,L_0630,,1
WS2812B,D9,LED_WS2812B-Mini_PLCC4_3.5x3.5mm,,1
MountingHole,H3,MountingHole_2.2mm_M2,,1
u1,C10,C_0805_2012Metric_Pad1.18x1.45mm_HandSolder,,1
WS2812B,D8,LED_WS2812B-Mini_PLCC4_3.5x3.5mm,,1
56p,C82,R_0805_2012Metric_Pad1.20x1.40mm_HandSolder,,1
u1,C21,C_0805_2012Metric_Pad1.18x1.45mm_HandSolder,,1
WS2812B,D2,LED_WS2812B-Mini_PLCC4_3.5x3.5mm,,1
10u/35V,C80,C_1206_3216Metric_Pad1.33x1.80mm_HandSolder,,1
AO6800-HXY,Q2,SOT-23-6_Handsoldering,,1
WS2812B,D3,LED_WS2812B-Mini_PLCC4_3.5x3.5mm,,1
10u,C9,C_0805_2012Metric_Pad1.18x1.45mm_HandSolder,,1
u1,C11,C_0805_2012Metric_Pad1.18x1.45mm_HandSolder,,1
u1,C18,C_0805_2012Metric_Pad1.18x1.45mm_HandSolder,,1
WS2812B,D11,LED_WS2812B-Mini_PLCC4_3.5x3.5mm,,1
u1,C14,C_0805_2012Metric_Pad1.18x1.45mm_HandSolder,,1
10k,R60,R_0805_2012Metric_Pad1.20x1.40mm_HandSolder,,1
22u,C83,R_0805_2012Metric_Pad1.20x1.40mm_HandSolder,,1
1k,R56,R_0805_2012Metric_Pad1.20x1.40mm_HandSolder,,1
M1,R59,R_0805_2012Metric_Pad1.20x1.40mm_HandSolder,,1
u1,C19,C_0805_2012Metric_Pad1.18x1.45mm_HandSolder,,1
1k,R58,R_0805_2012Metric_Pad1.20x1.40mm_HandSolder,,1
TPS54202DDC,U27,SOT-23-6_Handsoldering,,1
1k,R55,R_0805_2012Metric_Pad1.20x1.40mm_HandSolder,,1
RotaryEncoder,SW3,Encoder Alps-Alpine EC35,,1
u1,C25,C_0805_2012Metric_Pad1.18x1.45mm_HandSolder,,1
u1,C13,C_0805_2012Metric_Pad1.18x1.45mm_HandSolder,,1
ToBase,J5,Hirose_FH12-14S-0.5SH_1x14-1MP_P0.50mm_Horizontal_handsolder,,1
74AHCT1G125,U5,SOT-353_SC-70-5_Handsoldering,,1
